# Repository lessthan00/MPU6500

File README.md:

# MPU6500

[MPU6500](https://www.jlc-smt.com/lcsc/detail?componentCode=C50278)
姿态传感器/陀螺仪

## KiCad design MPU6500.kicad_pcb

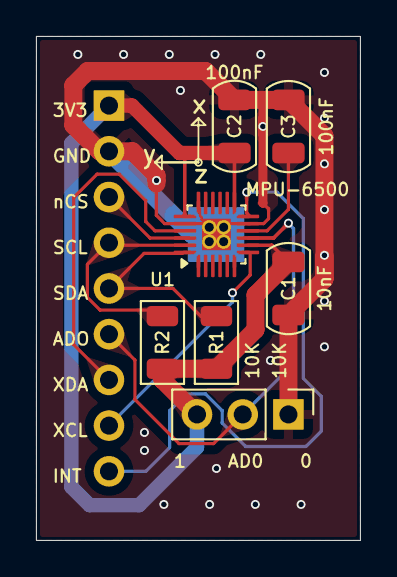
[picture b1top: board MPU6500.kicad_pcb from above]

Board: 2 copper layers, 18.0 x 28.0 mm, 8 parts (1 on the bottom side), 10 nets.

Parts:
C1: 10nF; C_1206_3216Metric
C2, C3: 100nF; C_1206_3216Metric
J1: Conn_01x03; PinHeader_1x03_P2.54mm_Vertical
J2: Conn_01x09; PinHeader_1x09_P2.54mm_Vertical
R1, R2: 10K; R_1206_3216Metric
U1: MPU-6500; QFN-24-1EP_3x3mm_P0.4mm_EP1.75x1.6mm_ThermalVias

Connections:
+3.3V: C1.1, C2.1, J1.3, J2.1, R1.1, R2.1, U1.8 (VDDIO), U1.13 (VDD), U1.19 (RESV)
/AUX_CL: J2.8, U1.7 (AUX_SCL)
/AUX_DA: J2.7, U1.21 (AUX_DA)
/IIC_AD0: J1.2, J2.6, U1.9 (SDO/AD0)
/IIC_SCL: J2.4, R2.2, U1.23 (SCL/SCLK)
/IIC_SDA: J2.5, R1.2, U1.24 (SDA/SDI)
/INT: J2.9, U1.12 (INT)
/nCS: J2.3, U1.22 (nCS)
GND: C1.2, C2.2, C3.1, J1.1, J2.2, U1.11 (FSYNC), U1.18 (GND), U1.20 (RESV), U1.25 (GND)
unnamed: C3.2, U1.10 (REGOUT)
